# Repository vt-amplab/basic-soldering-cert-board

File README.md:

basic-soldering-cert-board
==========================

Kicad files for the new basic soldering certification board

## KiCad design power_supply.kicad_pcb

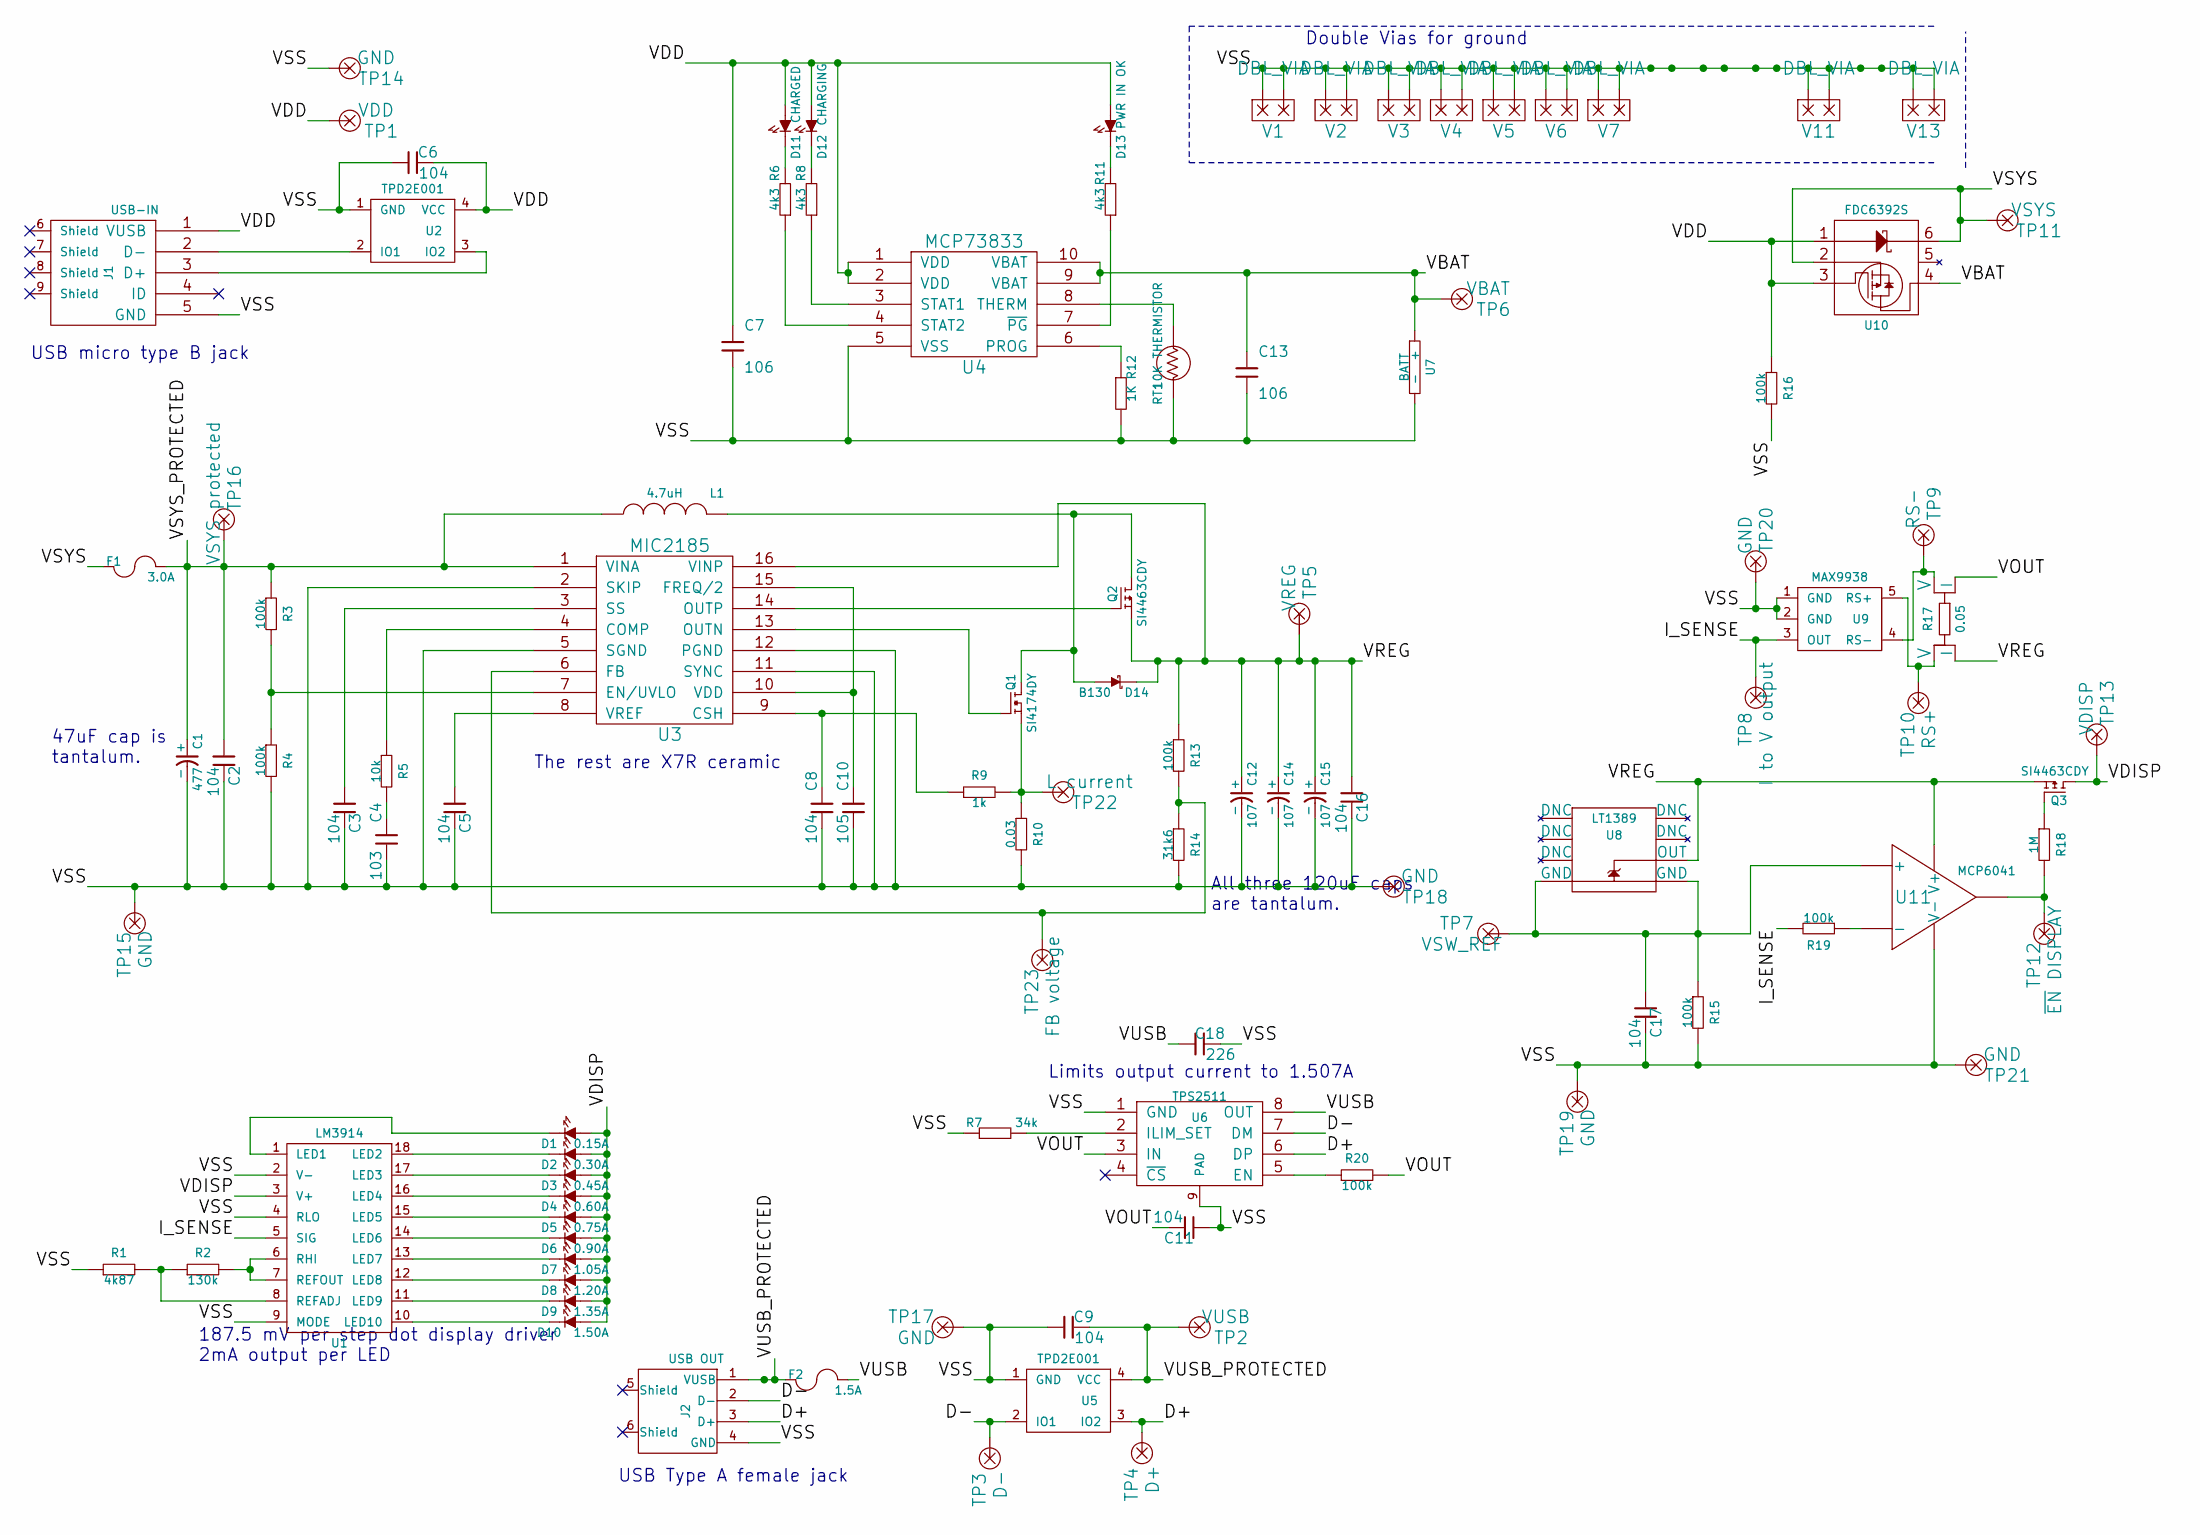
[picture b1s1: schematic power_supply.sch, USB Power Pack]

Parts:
C1: 477; c_2917_tant
C2, C3, C5, C6, C9, C11, C16, C17: 104; c_1206
C4: 103; cp_2.54mm
C7, C13: 106; c_1206
C8: 104; cp_2.54mm
C10: 105; cp_2.54mm
C12, C14, C15: 107; c_2924_tant
C18: 226; c_1206
D1: 0.15A; led_1206
D2: 0.30A; led_1206
D3: 0.45A; led_1206
D4: 0.60A; led_1206
D5: 0.75A; led_1206
D6: 0.90A; led_1206
D7: 1.05A; led_1206
D8: 1.20A; led_1206
D9: 1.35A; led_1206
D10: 1.50A; led_1206
D11: CHARGED; led_1206
D12: CHARGING; led_1206
D13: PWR IN OK; led_1206
D14: B130; diode_do41
F1: 3.0A; ptc_1812
F2: 1.5A; ptc_1812
J1: USB-IN; A108263CT(uUSB)
J2: USB OUT; A107360(USB-A)
L1: 4.7uH; ind_12.5mm
Q1: SI4174DY; si4174dy
Q2, Q3: SI4463CDY; si4463cdy
R1: 4k87; r_pth_2.5x6.5mm
R2: 130k; r_pth_2.5x6.5mm
R3, R4, R13, R15, R16, R19, R20: 100k; r_1206
R5: 10k; r_pth_2.5x6.5mm
R6, R8, R11: 4k3; r_pth_2.5x6.5mm
R7: 34k; r_pth_2.5x6.5mm
R9: 1k; r_1206
R10: 0.03; r_1206
R12: 1K; r_1206
R14: 31k6; r_1206
R17: 0.05; 1206-Kelvin
R18: 1M; r_pth_2.5x6.5mm
RT1: 10K THERMISTOR; r_1206
TP1: VDD; TP
TP2: VUSB; TP
TP3: D-; TP
TP4: D+; TP
TP5: VREG; TP
TP6: VBAT; TP
TP7: VSW_REF; TP
TP8: I to V output; TP
TP9: RS-; TP
TP10: RS+; TP
TP11: VSYS; TP
TP12: ~EN DISPLAY; TP
TP13: VDISP; TP
TP14, TP15, TP17, TP18, TP19, TP20, TP21: GND; TP
TP16: VSYS protected; TP
TP22: L current; TP
TP23: FB voltage; TP
U1: LM3914; PDIP-18
U2, U5: TPD2E001; TO-253-4
U3: MIC2185; so-16
U4: MCP73833; msop-10
U6: TPS2511; msop-8-powerpad
U7: BATT; BAT-18650-cylinder
U8: LT1389; so-8
U9: MAX9938; sot23-5
U10: FDC6392S; sot23-6
U11: MCP6041; so-8
V1, V2, V3, V4, V5, V6, V7, V11, V13: DBL_VIA

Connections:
/D+: J2.3 (D+), TP4.1, U5.3 (IO2), U6.6 (DP)
/D-: J2.2 (D-), TP3.1, U5.2 (IO1), U6.7 (DM)
/I_SENSE: R19.2, TP8.1, U1.5 (SIG), U9.3 (OUT)
/VBAT: C13.1, TP6.1, U4.9 (VBAT), U4.10 (VBAT), U7.1 (+), U10.4
/VDD: C6.2, C7.1, D11.1 (A), D12.1 (A), D13.1 (A), J1.1 (VUSB), R16.1, TP1.1, U2.4 (VCC), U4.1 (VDD), U4.2 (VDD), U10.1, U10.3
/VDISP: D1.1 (A), D2.1 (A), D3.1 (A), D4.1 (A), D5.1 (A), D6.1 (A), D7.1 (A), D8.1 (A), D9.1 (A), D10.1 (A), Q3.D, TP13.1, U1.3 (V+)
/VOUT: C11.2, R17.I2 (I), R20.2, U6.3 (IN)
/VREG: C12.1 (+), C14.1 (+), C15.1 (+), C16.1, D14.2, Q2.S, Q3.S, R13.1, R17.I1 (I), TP5.1, U3.16 (VINP), U8.6 (OUT), U11.7 (V+)
/VSS: C1.2 (-), C2.2, C3.2, C4.2, C5.2, C6.1, C7.2, C8.2, C9.1, C10.2, C11.1, C12.2 (-), C13.2, C14.2 (-), C15.2 (-), C16.2, C17.2, C18.2, J1.5 (GND), J2.4 (GND), R1.1, R4.2, R7.1, R10.2, R12.2, R14.2, R15.2, R16.2, RT1.2, TP14.1, TP15.1, TP17.1, TP18.1, TP19.1, TP20.1, TP21.1, U1.2 (V-), U1.4 (RLO), U1.9 (MODE), U2.1 (GND), U3.2 (SKIP), U3.5 (SGND), U3.11 (SYNC), U3.12 (PGND), U4.5 (VSS), U5.1 (GND), U6.1 (GND), U6.9 (PAD), U7.2 (-), U9.1 (GND), U9.2 (GND), U11.4 (V-), V1.1, V1.2, V2.1, V2.2, V3.1, V3.2, V4.1, V4.2, V5.1, V5.2, V6.1, V6.2, V7.1, V7.2, V11.1, V11.2, V13.1, V13.2
/VSYS: F1.1, TP11.1, U10.2, U10.6
/VSYS_PROTECTED: C1.1 (+), C2.1, F1.2, L1.1, R3.1, TP16.1, U3.1 (VINA)
/VUSB: C18.1, F2.2, U6.8 (OUT)
/VUSB_PROTECTED: C9.2, F2.1, J2.1 (VUSB), TP2.1, U5.4 (VCC)
unnamed: R11.1, U4.7 (~PG)
unnamed: D13.2 (K), R11.2
unnamed: R1.2, R2.1, U1.8 (REFADJ)
unnamed: R7.2, U6.2 (ILIM_SET)
unnamed: R20.1, U6.5 (EN)
unnamed: Q3.G, R18.1
unnamed: R12.1, U4.6 (PROG)
unnamed: RT1.1, U4.8 (THERM)
unnamed: D11.2 (K), R6.2
unnamed: D12.2 (K), R8.2
unnamed: D1.2 (K), U1.1 (LED1)
unnamed: R2.2, U1.6 (RHI), U1.7 (REFOUT)
unnamed: D5.2 (K), U1.15 (LED5)
unnamed: D10.2 (K), U1.10 (LED10)
unnamed: D9.2 (K), U1.11 (LED9)
unnamed: D8.2 (K), U1.12 (LED8)
unnamed: D7.2 (K), U1.13 (LED7)
unnamed: D6.2 (K), U1.14 (LED6)
unnamed: D4.2 (K), U1.16 (LED4)
unnamed: D3.2 (K), U1.17 (LED3)
unnamed: D2.2 (K), U1.18 (LED2)
unnamed: R17.V2 (V), TP9.1, U9.4 (RS-)
unnamed: R17.V1 (V), TP10.1, U9.5 (RS+)
unnamed: R13.2, R14.1, TP23.1, U3.6 (FB)
unnamed: J1.2 (D-), U2.2 (IO1)
unnamed: J1.3 (D+), U2.3 (IO2)
unnamed: R18.2, TP12.1, U11.6
unnamed: C17.1, R15.1, TP7.1, U8.4 (GND), U8.5 (GND), U11.3 (+)
unnamed: R19.1, U11.2 (-)
unnamed: R6.1, U4.4 (STAT2)
unnamed: Q1.G, U3.13 (OUTN)
unnamed: R5.1, U3.4 (COMP)
unnamed: C4.1, R5.2
unnamed: C5.1, U3.8 (VREF)
unnamed: C10.1, U3.10 (VDD), U3.15 (FREQ/2)
unnamed: Q2.G, U3.14 (OUTP)
unnamed: R3.2, R4.1, U3.7 (EN/UVLO)
unnamed: C3.1, U3.3 (SS)
unnamed: R8.1, U4.3 (STAT1)
unnamed: D14.1, L1.2, Q1.D, Q2.D
unnamed: C8.1, R9.1, U3.9 (CSH)
unnamed: Q1.S, R9.2, R10.1, TP22.1

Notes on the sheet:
187.5 mV per step dot display driver 2mA output per LED
USB Type A female jack
USB micro type B jack
All three 120uF caps are tantalum.
47uF cap is tantalum.
Limits output current to 1.507A
The rest are X7R ceramic
Double Vias for ground

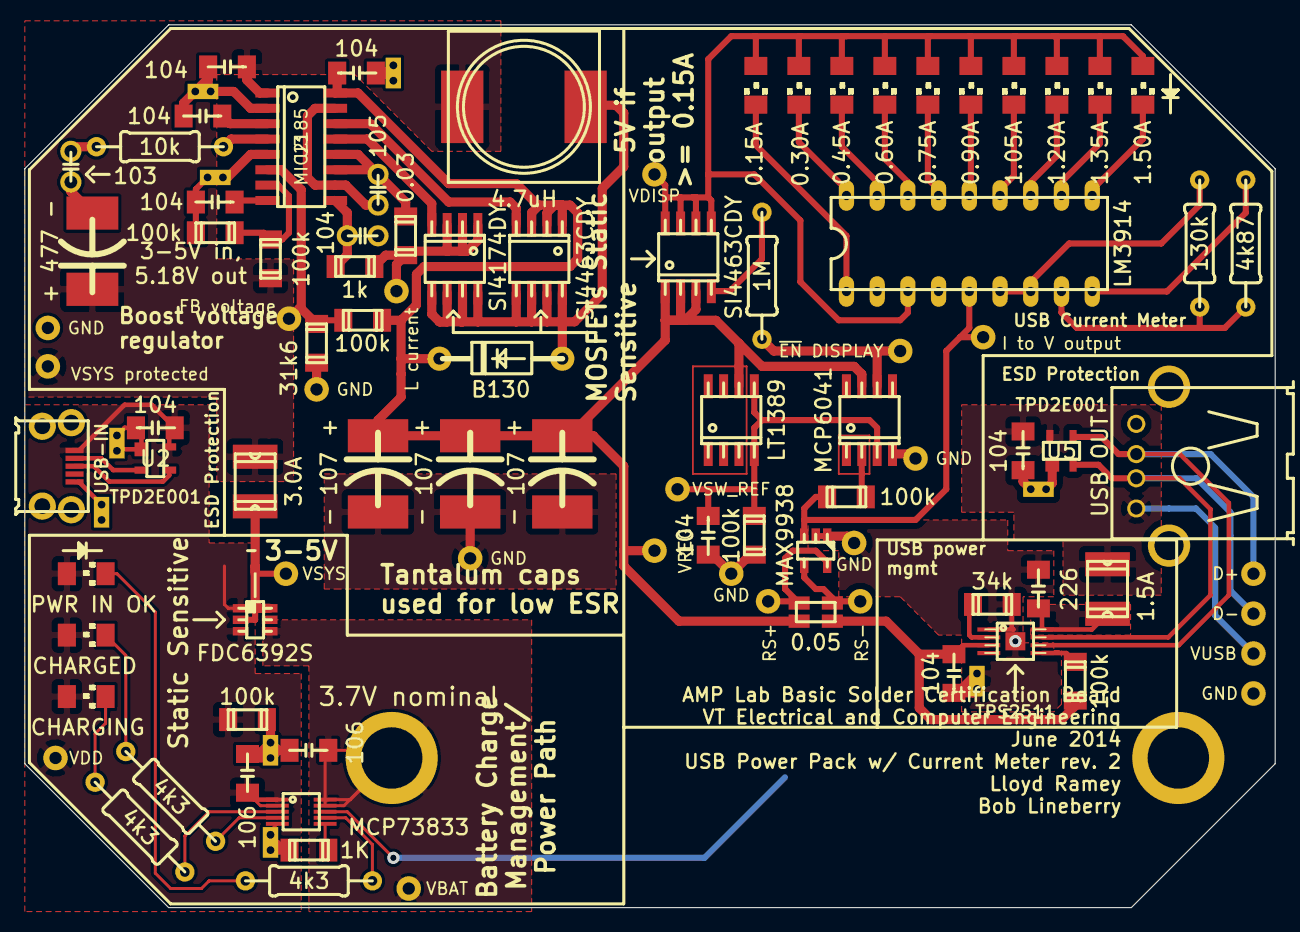
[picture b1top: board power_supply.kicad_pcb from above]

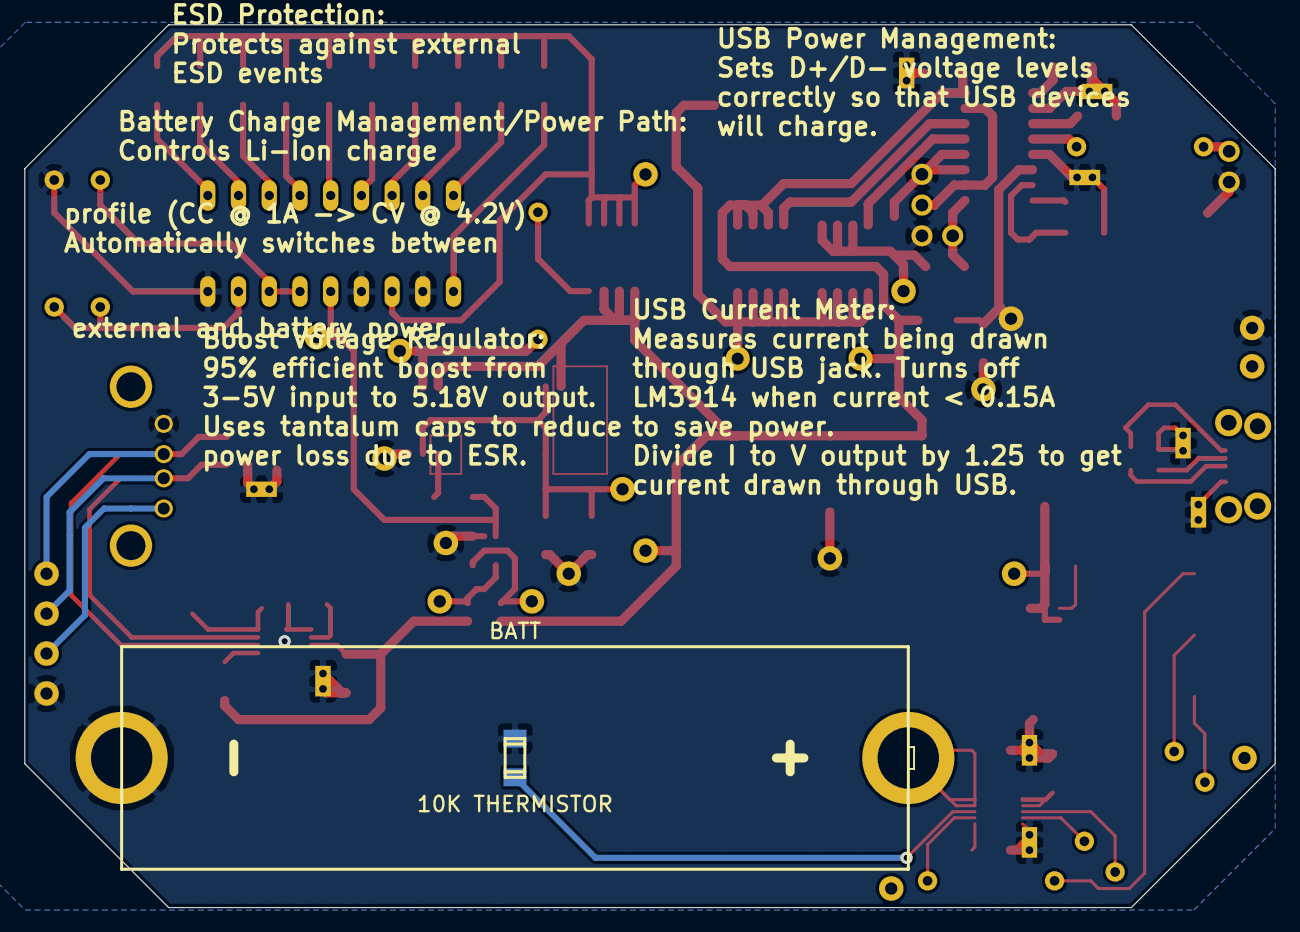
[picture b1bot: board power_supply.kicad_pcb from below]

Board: 2 copper layers, 103.4 x 73.0 mm, 104 parts (2 on the bottom side), 55 nets.

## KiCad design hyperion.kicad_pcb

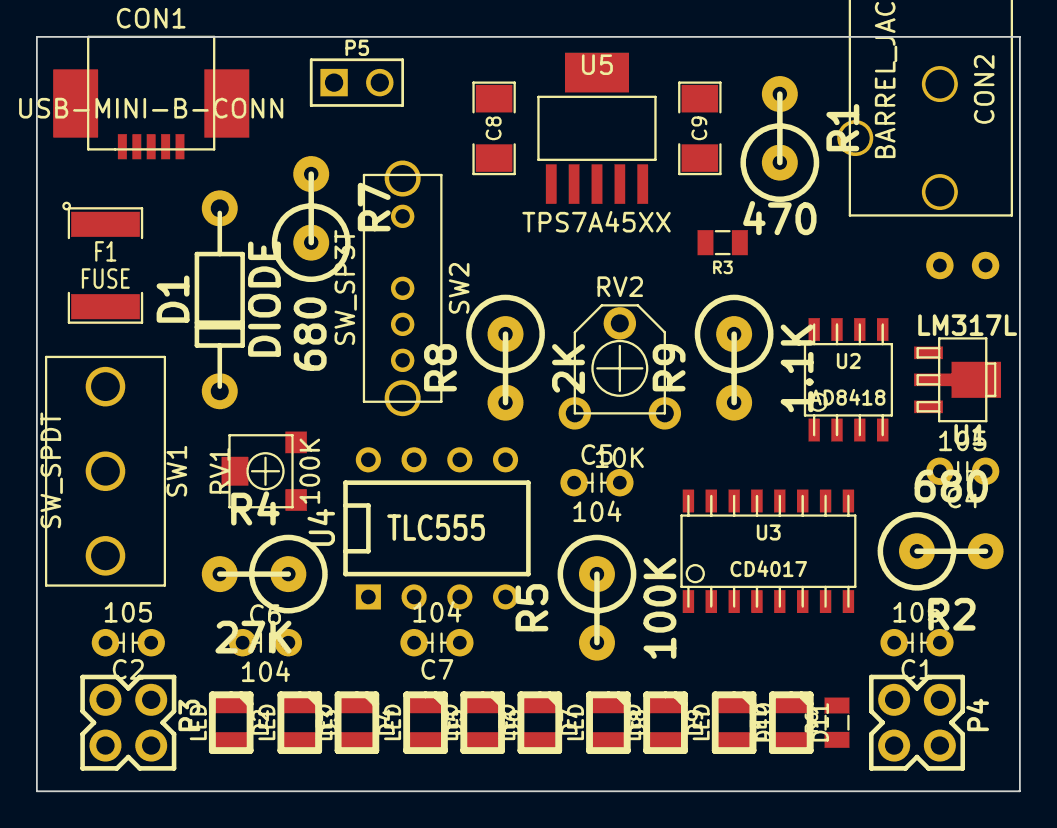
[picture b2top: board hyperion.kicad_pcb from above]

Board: 2 copper layers, 54.6 x 41.9 mm, 44 parts (1 on the bottom side), 29 nets, no tracks yet.

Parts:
C1, C2, C4: 105; CAP
C3, C5, C6, C7: 104; CAP
C8, C9: 106; SM1206
CON1: USB-MINI-B-CONN; USB_MINI_B_SMD_NO_TACK
CON2: BARREL_JACK; Barrel_Jack
D1: DIODE; diode_do41
D2, D3, D4, D5, D6, D7, D8, D9, D10, D11: LED; Cree_CLM3C
F1: FUSE; SM1812
P3: LEFT; PIN_ARRAY_2X2_CUSTOM
P4: RIGHT; PIN_ARRAY_2X2_CUSTOM
P5: Spring Terminal; PIN_ARRAY_2X1
R1: 470; rc07_vert
R2, R7: 680; rc07_vert
R3: .05; SM0805_Custom
R4: 27K; rc07_vert
R5: 100K; rc07_vert
R6: 100; SM0805_Custom
R8: 2K; rc07_vert
R9: 1.1K; rc07_vert
RV1: 100K; POT_JLEAD
RV2: 10K; POT_PCPIN
SW1: SW_SPDT; SW_SPDT_CUSTOM
SW2: SW_SP3T
U1: LM317L; sot89
U2: AD8418; so-8
U3: CD4017; so-16
U4: TLC555; DIP-8__300
U5: TPS7A45XX; SOT-223-6

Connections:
/Connectors/GND: C1.1, C2.1, C3.1, C4.2, C5.2, C6.1, C7.2, C8.2, C9.2, CON1.5, CON2.2, CON2.3, P3.2, P3.4, P4.2, P4.4, P5.1, R2.2, R6.2, R7.2, U2.2, U3.8, U3.13, U3.15, U4.1, U5.1, U5.3, U5.6
/Connectors/VHIGH: F1.2, SW1.2
/Connectors/V_IN: CON1.1, CON2.1, D1.1, P5.2
/Main Regulator/VH: C8.1, R3.2, U2.8, U5.2
/Main Regulator/VOUT: C1.2, C2.2, C9.1, P3.1, P3.3, P4.1, P4.3, R8.1, R9.1, RV2.2, RV2.3, U5.4
/Monitor/LED_CLK: U3.14, U4.3
/Monitor/VCONTROL: C5.1, U2.5, U4.5
/Monitor/VIN: C3.2, R3.1, SW1.1, U1.1, U2.1
/Monitor/VLED: C4.1, C7.1, R1.1, R5.2, U1.2, U2.3, U2.6, U2.7, U3.16, U4.4, U4.8
unnamed: D1.2, F1.1
unnamed: RV2.1, SW2.4
unnamed: R7.1, SW2.2, U5.5
unnamed: R8.2, SW2.3
unnamed: R9.2, SW2.1
unnamed: R4.2, RV1.1
unnamed: R5.1, RV1.2, RV1.3, U4.7
unnamed: C6.2, R4.1, U4.2, U4.6
unnamed: D11.1, U3.11
unnamed: D9.1, U3.6
unnamed: D7.1, U3.1
unnamed: D2.2, D3.2, D4.2, D5.2, D6.2, D7.2, D8.2, D9.2, D10.2, D11.2, R6.1
unnamed: D5.1, U3.7
unnamed: D3.1, U3.2
unnamed: D6.1, U3.10
unnamed: D10.1, U3.9
unnamed: D4.1, U3.4
unnamed: D2.1, U3.3
unnamed: D8.1, U3.5
unnamed: R1.2, R2.1, U1.3

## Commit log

2014-03-24 Added dim
2014-03-24 Beginning PCB.
    Need to get dimensions of breadboard
2014-03-31 Updated project file
2014-03-31 Added gitignore
2014-03-31 Rearranged, added a few things (look at long msg).
    Renamed to power_supply (boring, but more professional).
    Rearranged schematic to look somewhat organized.
    Added more description.
    Added Li-Ion charger circuit.
    Added Phone charger output w/ adjustable resistors on data lines.
    Added over voltage protection for phone charger and Li-Ion charger (cuts
2014-03-31 Corrected name.
    Rearranged schematic.
2014-03-31 Updated schematic
2014-03-31 Updated from bob feedback
2014-04-21 Updating to new design
2014-06-13 Purged rev 1 to begin rev 2
2014-06-13 Updated libraries
2014-06-13 MSP73833 circuit stuff
2014-06-14 Updated library. Began adding components.
2014-06-15 Power Supply Schematic
    Completed schematic up through the MIC2185
    Regulated output voltage named VpREG
    Custom components listed in power_supply-cache.lib
2014-06-15 Updated component library
2014-06-16 Finished schematic
2014-06-17 Added ESD protection to input and output.
2014-06-17 Updated comments
2014-06-17 Updated product numbers
    Also modified current sense schematic to reflect eval board suggestions
2014-06-17 Added LM3914 digikey product number
2014-06-17 Added comments
2014-06-18 Updated library
2014-06-18 Updating based on Bob's feedback
2014-06-18 Added turn off for display when no current is being drawn
2014-06-18 Fixed a few issues with printout
2014-06-18 Fixed ERC errors
2014-06-19 Updated comparator circuit to add histeresis.
    Should turn on at .187V and off at .157V
2014-06-19 Updated display auto-off circuit, added part numbers
2014-06-20 Began creating footprints
2014-06-20 Finished footprints. Began layout
2014-06-20 Finished rev1 layout
2014-06-21 Began routing.
    Fixed a few footprint issues.
    Added through hole vias.
2014-06-22 More routing work
2014-06-22 Finished routing
2014-06-24 Fixed issues in response to Bob's comments
2014-06-24 More fixes
2014-06-24 Added test points
2014-06-25 Added silkscreen
2014-06-26 Updated silkscreen
2014-06-26 Removed lock file
2014-06-26 updated gitignore
2014-06-26 Removed unused files
2014-06-29 Corrected rsense for regulator
2014-07-17 Updated files
2014-07-28 Reshaping board
2014-07-28 Filled ground plane
2014-07-28 Fixed silkscreen after reshaping
2014-07-30 Updated schematic
    Added output capacitor onto TPS2511, pull up on EN
    Updated board shape
2014-08-01 Fixed schematic, PCB, and library TPS2511
    TPS2511 GND and VCC were switched.
2014-08-01 Fixed MAX9938
    RS+/RS- reversed
2014-08-01 Fixed test points for RS+/-
    Reversed
